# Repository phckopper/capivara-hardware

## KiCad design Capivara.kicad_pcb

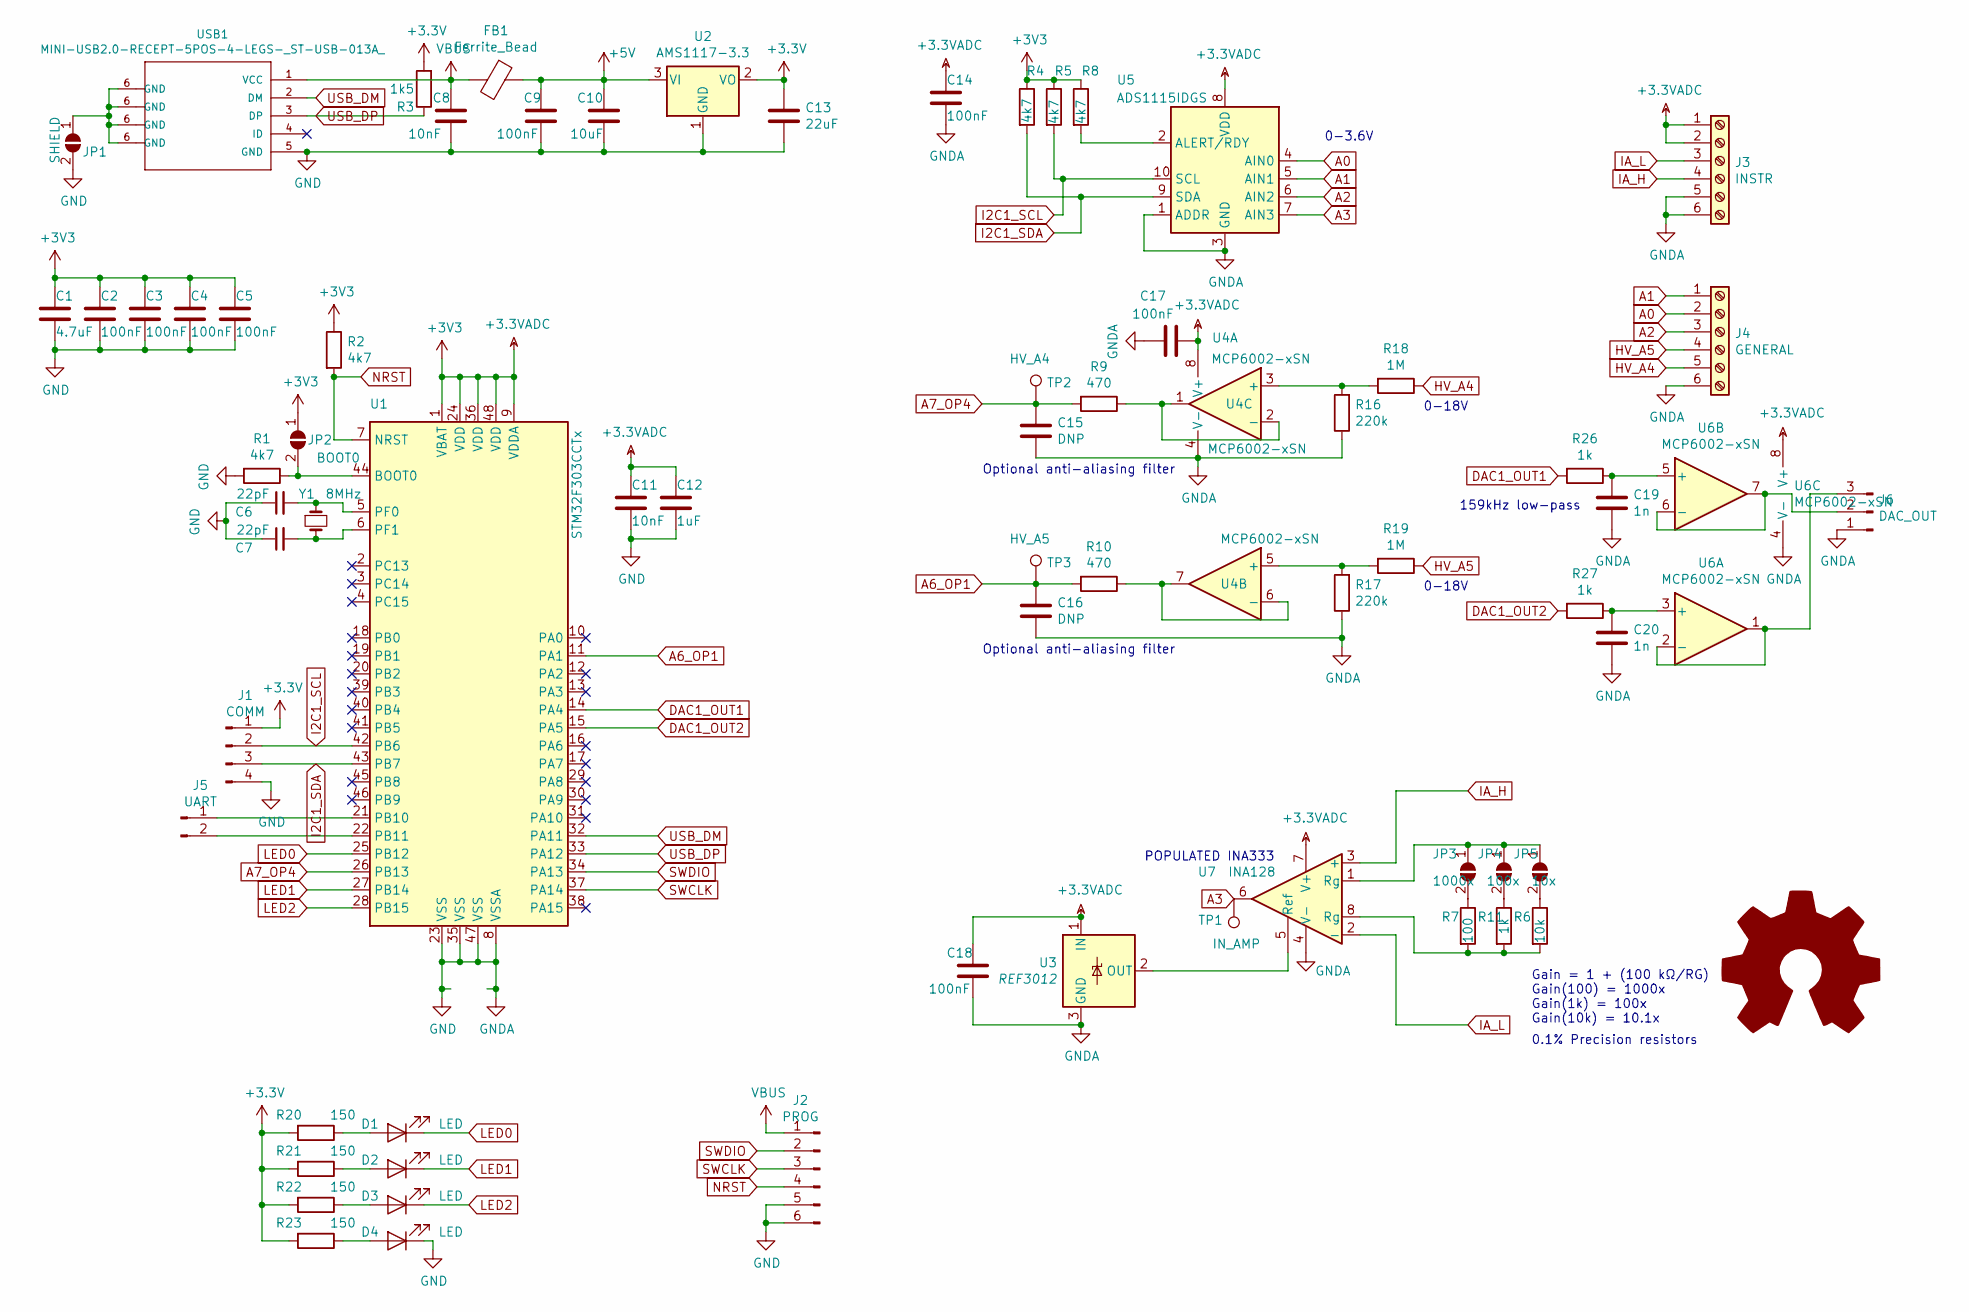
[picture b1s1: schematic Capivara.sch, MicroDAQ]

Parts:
C1: 4.7uF; R0603
C2, C3, C4, C5, C9, C14, C17, C18: 100nF; R0603
C6, C7: 22pF; R0603
C8, C11: 10nF; R0603
C10: 10uF; R0603
C12: 1uF; R0603
C13: 22uF; R0805
C15, C16: DNP; C0603
C19, C20: 1n; C0603
D1, D2, D3, D4: LED; LED_0603_1608Metric
FB1: Ferrite_Bead; L0603
J1: COMM; PinHeader_1x04_P2.54mm_Vertical
J2: PROG; PinHeader_1x06_P2.54mm_Vertical
J3: INSTR; TerminalBlock_Phoenix_MPT-0,5-6-2.54_1x06_P2.54mm_Horizontal
J4: GENERAL; TerminalBlock_Phoenix_MPT-0,5-6-2.54_1x06_P2.54mm_Horizontal
J5: UART; PinHeader_1x02_P2.54mm_Vertical
J6: DAC_OUT; PinHeader_1x03_P2.54mm_Vertical
JP1: SHIELD; SolderJumper-2_P1.3mm_Open_Pad1.0x1.5mm
JP2: BOOT0; SolderJumper-2_P1.3mm_Open_RoundedPad1.0x1.5mm
JP3: 1000x; SolderJumper-2_P1.3mm_Open_RoundedPad1.0x1.5mm
JP4: 100x; SolderJumper-2_P1.3mm_Open_RoundedPad1.0x1.5mm
JP5: 10x; SolderJumper-2_P1.3mm_Open_RoundedPad1.0x1.5mm
R1, R2, R4, R5, R8: 4k7; R0603
R3: 1k5; R0603
R6: 10k; R0603
R7: 100; R0603
R9, R10: 470; R0603
R11, R26, R27: 1k; R0603
R16, R17: 220k; R0603
R18, R19: 1M; R0603
R20, R21, R22, R23: 150; R0603
TP1: IN_AMP; TestPoint_Pad_D2.0mm
TP2: HV_A4; TestPoint_Pad_D2.0mm
TP3: HV_A5; TestPoint_Pad_D2.0mm
U1: STM32F303CCTx; LQFP-48_7x7mm_P0.5mm
U2: AMS1117-3.3; SOT-223-3_TabPin2
U3: REF3012; SOT-23
U4, U6: MCP6002-xSN; SOIC8-1.27-5X4MM
U5: ADS1115IDGS; TSSOP-10_3x3mm_P0.5mm
U7: INA128; VSSOP-8_3.0x3.0mm_P0.65mm
USB1: MINI-USB2.0-RECEPT-5POS-4-LEGS-_ST-USB-013A_; MINIUSB5+4P-0.8-90D; MPN ST-USB-013A
Y1: 8MHz; HC49US

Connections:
+5V: C9.1, C10.1, FB1.1, U2.3 (VI)
A0: J4.2, U5.4 (AIN0)
A1: J4.1, U5.5 (AIN1)
A2: J4.3, U5.6 (AIN2)
A3: TP1.1, U5.7 (AIN3), U7.6
A6_OP1: C16.1, R10.2, TP3.1, U1.11 (PA1)
A7_OP4: C15.1, R9.2, TP2.1, U1.26 (PB13)
DAC1_OUT1: R26.2, U1.14 (PA4)
DAC1_OUT2: R27.2, U1.15 (PA5)
GND: C1.2, C2.2, C3.2, C4.2, C5.2, C6.1, C7.1, C8.2, C9.2, C10.2, C11.2, C12.2, C13.2, C14.2, C15.2, C16.2, C17.2, C18.2, C19.2, C20.2, D4.1 (K), J1.4, J2.5, J2.6, J3.5, J3.6, J4.6, J6.1, JP1.2 (B), R1.2, R16.1, R17.1, U1.8 (VSSA), U1.23 (VSS), U1.35 (VSS), U1.47 (VSS), U2.1 (GND), U3.3 (GND), U4.4 (V-), U5.1 (ADDR), U5.3 (GND), U6.4 (V-), U7.4 (V-), USB1.5 (GND)
HV_A4: J4.5, R18.1
HV_A5: J4.4, R19.1
I2C1_SCL: J1.2, R5.2, U1.42 (PB6), U5.10 (SCL)
I2C1_SDA: J1.3, R4.2, U1.43 (PB7), U5.9 (SDA)
IA_H: J3.4, U7.3 (+)
IA_L: J3.3, U7.2 (-)
LED0: D1.1 (K), U1.25 (PB12)
LED1: D2.1 (K), U1.27 (PB14)
LED2: D3.1 (K), U1.28 (PB15)
NRST: J2.4, R2.2, U1.7 (NRST)
unnamed: C6.2, U1.5 (PF0), Y1.1
unnamed: C7.2, U1.6 (PF1), Y1.2
unnamed: C19.1, R26.1, U6.5 (+)
unnamed: C20.1, R27.1, U6.3 (+)
unnamed: D1.2 (A), R20.1
unnamed: D2.2 (A), R21.1
unnamed: D3.2 (A), R22.1
unnamed: D4.2 (A), R23.1
unnamed: J5.1, U1.21 (PB10)
unnamed: J5.2, U1.22 (PB11)
unnamed: J6.2, U6.6 (-), U6.7
unnamed: J6.3, U6.1, U6.2 (-)
unnamed: JP1.1 (A), USB1.6 (GND)
unnamed: JP2.2 (B), R1.1, U1.44 (BOOT0)
unnamed: JP3.1 (A), JP4.1 (A), JP5.1 (A), U7.1 (Rg)
unnamed: JP3.2 (B), R7.1
unnamed: JP4.2 (B), R11.1
unnamed: JP5.2 (B), R6.1
unnamed: R8.2, U5.2 (ALERT/RDY)
unnamed: R9.1, U4.1, U4.2 (-)
unnamed: R10.1, U4.6 (-), U4.7
unnamed: R6.2, R7.2, R11.2, U7.8 (Rg)
unnamed: R16.2, R18.2, U4.3 (+)
unnamed: R17.2, R19.2, U4.5 (+)
unnamed: U3.2 (OUT), U7.5 (Ref)
SWCLK: J2.3, U1.37 (PA14)
SWDIO: J2.2, U1.34 (PA13)
USB_DM: U1.32 (PA11), USB1.2 (DM)
USB_DP: R3.1, U1.33 (PA12), USB1.3 (DP)
VBUS: C8.1, FB1.2, J2.1, USB1.1 (VCC)

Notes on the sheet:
0-18V
0-3.6V
Optional anti-aliasing filter
159kHz low-pass
Gain = 1 + (100 kΩ/RG) Gain(100) = 1000x Gain(1k) = 100x Gain(10k) = 10.1x
POPULATED INA333
0.1% Precision resistors

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
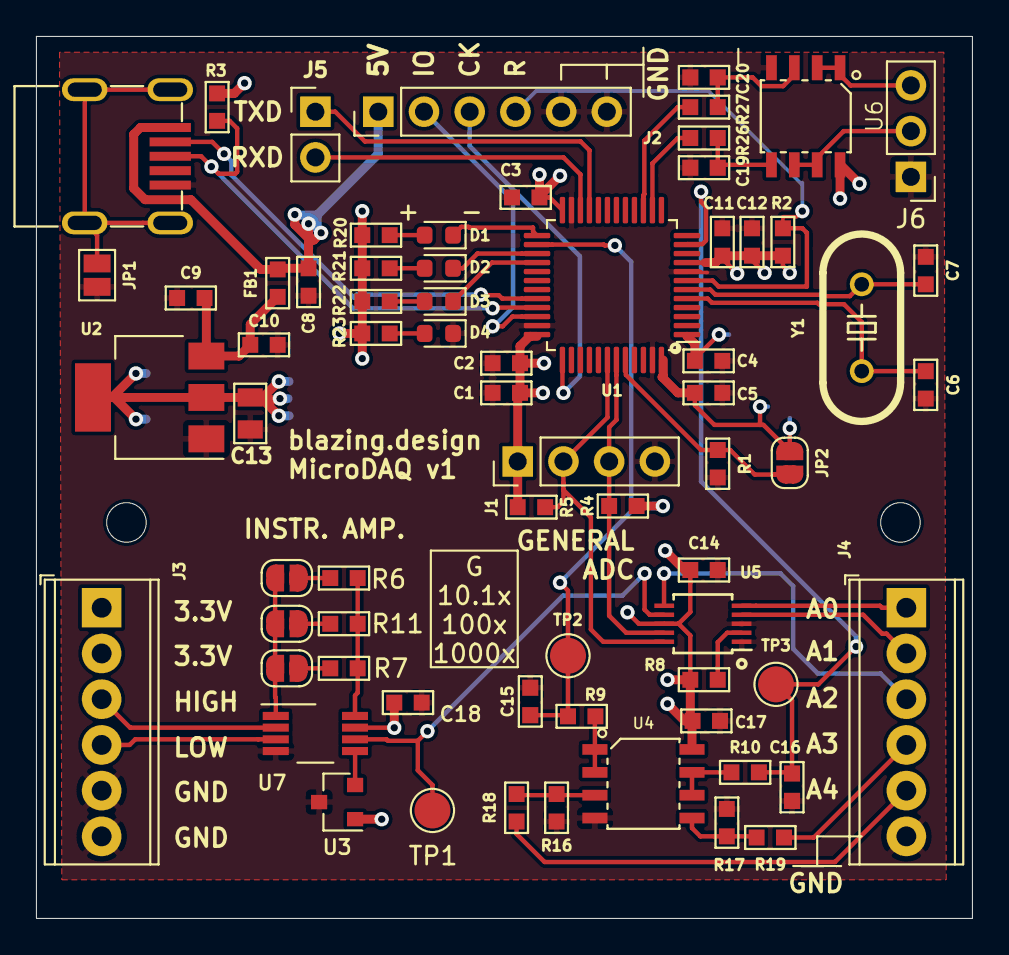
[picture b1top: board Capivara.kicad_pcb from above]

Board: 2 copper layers, 52.0 x 49.0 mm, 69 parts (0 on the bottom side), 51 nets.

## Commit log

2019-05-14 Add fab files
2019-05-15 Mudanças Pezzi
2019-05-20 Usar INA ao invés de InsOp discreto
